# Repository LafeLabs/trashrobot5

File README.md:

## [link up a level../](../)

# Trash robot

## UNO Shield

[link to page on pcbway to buy board](https://www.pcbway.com/project/shareproject/Generic_Trash_Robot_UNO_Shield__V5.html)

## UNO Shield BOM

| REFDES|value| source/part#| 
|-------|-----|-------------|
|   R1  | 10k | [digikey RNCP0603FTD10K0CT-ND](https://www.digikey.com/product-detail/en/panasonic-electronic-components/ERJ-3EKF3301V/P3.30KHCT-ND/1746762)  | 
|   R2  | 10k | [digikey RNCP0603FTD10K0CT-ND](https://www.digikey.com/product-detail/en/panasonic-electronic-components/ERJ-3EKF3301V/P3.30KHCT-ND/1746762)  | 
|   R3  | 10k | [digikey RNCP0603FTD10K0CT-ND](https://www.digikey.com/product-detail/en/panasonic-electronic-components/ERJ-3EKF3301V/P3.30KHCT-ND/1746762)  | 
|   R4  | 300 | [digikey RR08P300DCT-ND](https://www.digikey.com/product-detail/en/susumu/RR0816P-301-D/RR08P300DCT-ND/432711)  | 
|   R5  |10k pot| [digikey PTV09A-4225F-B103-ND](https://www.digikey.com/product-detail/en/bourns-inc/PTV09A-4225F-B103/PTV09A-4225F-B103-ND/3781155)  | 
|   Q1  |MOSFET| [digikey IRLML0060TRPBFCT-ND](https://www.digikey.com/product-detail/en/infineon-technologies/IRLML0060TRPBF/IRLML0060TRPBFCT-ND/2202229)  | 
|   D1  |DIODE| [digikey S1BFSCT-ND](https://www.digikey.com/product-detail/en/on-semiconductor/S1B/S1BFSCT-ND/965719)  | 
|   C1  |1000uF| [digikey 1189-1745-ND](https://www.digikey.com/product-detail/en/rubycon/35PX1000MEFC10X20/1189-1745-ND/3563769)  | 
|   X1  |CONTACT| [digikey 277-6354-ND](https://www.digikey.com/product-detail/en/phoenix-contact/1984963/277-6354-ND/2513976)  | 
|   X2  |CONTACT| [digikey 277-6354-ND](https://www.digikey.com/product-detail/en/phoenix-contact/1984963/277-6354-ND/2513976)  | 
|   X3  |CONTACT| [digikey 277-6354-ND](https://www.digikey.com/product-detail/en/phoenix-contact/1984963/277-6354-ND/2513976)  | 
|   SW1  |BUTTON| [digikey P15931SCT-ND](https://www.digikey.com/product-detail/en/panasonic-electronic-components/EVQ-11D05B/P15931SCT-ND/3873336)  | 
|   SW2  |BUTTON| [digikey P15931SCT-ND](https://www.digikey.com/product-detail/en/panasonic-electronic-components/EVQ-11D05B/P15931SCT-ND/3873336)  | 
|   SW3  |SPDT| [digikey 360-1013-ND](https://www.digikey.com/product-detail/en/nkk-switches/B13AP/360-1013-ND/379100)  | 
|   J1  |3x HEADERS| [digikey SAM1029-03-ND](https://www.digikey.com/product-detail/en/samtec-inc/TSW-103-07-G-S/SAM1029-03-ND/1101324)| 
|   J2  |4x HEADERS| [digikey SAM1029-04-ND](https://www.digikey.com/product-detail/en/samtec-inc/TSW-104-07-G-S/SAM1029-04-ND/1101323)| 
|   J3  |5x HEADERS| [digikey SAM1029-05-ND](https://www.digikey.com/product-detail/en/samtec-inc/TSW-105-07-G-S/SAM1029-05-ND/1101322)| 
|   J4  |ARDUINO HEADERS| [digikey 1528-1074-ND](https://www.digikey.com/product-detail/en/adafruit-industries-llc/85/1528-1074-ND/5154649)|
|   JS1  |3X SOCKET| [digikey SAM1206-03-ND](https://www.digikey.com/product-detail/en/samtec-inc/SSQ-103-03-T-S/SAM1206-03-ND/1111955)|
|   JS2  |4X SOCKET| [digikey SAM1206-04-ND](https://www.digikey.com/product-detail/en/samtec-inc/SSQ-104-03-T-S/SAM1206-04-ND/1111954)|
|   JS3  |5X SOCKET| [digikey SAM1206-05-ND](https://www.digikey.com/product-detail/en/samtec-inc/SSQ-105-03-T-S/SAM1206-05-ND/1111953)|

## Dual H Bridge

[link to buy on PCBway](https://www.pcbway.com/project/shareproject/Dual_H_Bridge__V_5.html)

## Dual H Bridge BOM

| REFDES|value| source/part#| 
|-------|-----|-------------|
|   R1  | 10k | [digikey RNCP0603FTD10K0CT-ND](https://www.digikey.com/product-detail/en/panasonic-electronic-components/ERJ-3EKF3301V/P3.30KHCT-ND/1746762)  | 
|   R2  | 10k | [digikey RNCP0603FTD10K0CT-ND](https://www.digikey.com/product-detail/en/panasonic-electronic-components/ERJ-3EKF3301V/P3.30KHCT-ND/1746762)  | 
|   R3  | 10k | [digikey RNCP0603FTD10K0CT-ND](https://www.digikey.com/product-detail/en/panasonic-electronic-components/ERJ-3EKF3301V/P3.30KHCT-ND/1746762)  | 
|   R4  | 10k | [digikey RNCP0603FTD10K0CT-ND](https://www.digikey.com/product-detail/en/panasonic-electronic-components/ERJ-3EKF3301V/P3.30KHCT-ND/1746762)  | 
|   Q1  |MOSFET| [digikey IRLML0060TRPBFCT-ND](https://www.digikey.com/product-detail/en/infineon-technologies/IRLML0060TRPBF/IRLML0060TRPBFCT-ND/2202229)  | 
|   Q2  |MOSFET| [digikey IRLML0060TRPBFCT-ND](https://www.digikey.com/product-detail/en/infineon-technologies/IRLML0060TRPBF/IRLML0060TRPBFCT-ND/2202229)  | 
|   Q3  |MOSFET| [digikey IRLML0060TRPBFCT-ND](https://www.digikey.com/product-detail/en/infineon-technologies/IRLML0060TRPBF/IRLML0060TRPBFCT-ND/2202229)  | 
|   Q4  |MOSFET| [digikey IRLML0060TRPBFCT-ND](https://www.digikey.com/product-detail/en/infineon-technologies/IRLML0060TRPBF/IRLML0060TRPBFCT-ND/2202229)  | 
|   Q5  |MOSFET| [digikey IRLML0060TRPBFCT-ND](https://www.digikey.com/product-detail/en/infineon-technologies/IRLML0060TRPBF/IRLML0060TRPBFCT-ND/2202229)  | 
|   Q6  |MOSFET| [digikey IRLML0060TRPBFCT-ND](https://www.digikey.com/product-detail/en/infineon-technologies/IRLML0060TRPBF/IRLML0060TRPBFCT-ND/2202229)  | 
|   Q7  |MOSFET| [digikey IRLML0060TRPBFCT-ND](https://www.digikey.com/product-detail/en/infineon-technologies/IRLML0060TRPBF/IRLML0060TRPBFCT-ND/2202229)  | 
|   Q8  |MOSFET| [digikey IRLML0060TRPBFCT-ND](https://www.digikey.com/product-detail/en/infineon-technologies/IRLML0060TRPBF/IRLML0060TRPBFCT-ND/2202229)  | 
|   X1  |CONTACT| [digikey 277-6354-ND](https://www.digikey.com/product-detail/en/phoenix-contact/1984963/277-6354-ND/2513976)  | 
|   X2  |CONTACT| [digikey 277-6354-ND](https://www.digikey.com/product-detail/en/phoenix-contact/1984963/277-6354-ND/2513976)  | 
|   X3  |CONTACT| [digikey 277-6354-ND](https://www.digikey.com/product-detail/en/phoenix-contact/1984963/277-6354-ND/2513976)  | 
|   J1  |4x RA HEADERS| [digikey TSW-104-25-G-S-RA-ND](https://www.digikey.com/product-detail/en/samtec-inc/TSW-104-25-G-S-RA/TSW-104-25-G-S-RA-ND/7864906)| 
|   J2  |5x RA HEADERS| [digikey TSW-105-25-G-S-RA-ND](https://www.digikey.com/product-detail/en/samtec-inc/TSW-105-25-G-S-RA/TSW-105-25-G-S-RA-ND/2685928)| 
|   JS1  |4X SOCKET| [digikey SAM1206-04-ND](https://www.digikey.com/product-detail/en/samtec-inc/SSQ-104-03-T-S/SAM1206-04-ND/1111954)|
|   JS2  |5X SOCKET| [digikey SAM1206-05-ND](https://www.digikey.com/product-detail/en/samtec-inc/SSQ-105-03-T-S/SAM1206-05-ND/1111953)|

## Kit BOM

|Description|Link|
|-----------|----|
|Jumper Wires|[Digikey 1528-1160-ND](https://www.digikey.com/product-detail/en/adafruit-industries-llc/824/1528-1160-ND/5353620)|
|Solder Paste|[Digikey SMDLTLFP-ND](https://www.digikey.com/product-detail/en/chip-quik-inc/SMDLTLFP/SMDLTLFP-ND/2682721)|
|2.1X5 MM Barrel Breakout|[Digikey 839-1518-ND](https://www.digikey.com/product-detail/en/tensility-international-corp/10-02931/839-1518-ND/9686414)|
|2.1X5 MM Barrel patch cable|[Amazon $6.99](https://www.amazon.com/Valley-Enterprises%C2%AE-2-1mm-5-5mm-Adapter/dp/B00DX72UXW/)|
| 12V 12Ah LiPo|[Amazon $33.99](https://www.amazon.com/gp/product/B00ME3ZH7C/)|
| 12V 3Ah LiPo |[Amazon $24.19](https://www.amazon.com/TalentCell-Rechargeable-3000mAh-Lithium-External/dp/B01M7Z9Z1N/) |
|30 AWG Magnet wire|[Amazon $17.45](https://www.amazon.com/dp/B07SG4CPSF/) |
| Arduino Uno | [Amazon $8.49](https://www.amazon.com/HiLetgo-ATmega328P-Development-Compatible-Microcontroller/dp/B01AR7YJ3O/) |
| Hookup Wire Kit | [Adafruit $19.95](https://www.adafruit.com/product/3111) |
| 3 axis Accelerometer | [Adafruit $7.95](https://www.adafruit.com/product/2019) |
| I2C Pressure Sensor| [Adafruit $9.95](https://www.adafruit.com/product/2651) |
|ultrasonic range finder|[Sparkfun $3.95](https://www.sparkfun.com/products/15569)|
| Neopixel 8x array| [Adafruit $5.95](https://www.adafruit.com/product/1426) |
| Hot Air Rework Tool| [Sparkfun $129.95](https://www.sparkfun.com/products/14557) |
| Soldering Iron| [Sparkfun $129.00](https://www.sparkfun.com/products/14734) |
| Lead Free Solder| [Sparkfun $7.95](https://www.sparkfun.com/products/9325) |

- [boards/unoshield-v5.brd](boards/unoshield-v5.brd)
- [boards/unoshield-v5.sch](boards/unoshield-v5.sch)
- [boards/unoshield-v5-bom.xlsx](boards/unoshield-v5-bom.xlsx)
- [boards/dualHbridge-v5.brd](boards/dualHbridge-v5.brd)
- [boards/dualHbridge-v5.sch](boards/dualHbridge-v5.sch)
- [boards/dualHbridge-v5bom.xlsx](boards/dualHbridge-v5bom.xlsx)

### Cables:

- 4 conductor, 8 inches long, header to stripped and tinned ends with 1/4 inch stripping: [IDSS-04-S-08.00-ST4](https://www.samtec.com/products/idss-04-s-08.00-st4)
- 3 conductor, 8 inches long, header to stripped and tinned ends, with 1/4 inch stripping: [https://www.samtec.com/products/idss-03-s-08.00-st4](https://www.samtec.com/products/idss-03-s-08.00-st4)

# 90 degree terminal strips for dual h bridge:

5 pin:
TSW-105-25-G-S-RA	

4 pin:

TSW-104-25-G-S-RA

## 5 wire cable from shield to dual h bridge:

idss-05-d-06.00

## 4 wire cable to solder stripped ends for stepper motor and also I2C sensors(need as many of these as stepper motors plus I2 C sensors.):

IDSS-04-S-08.00-T	(8 inches)

## 3 wire cable with solder tinned ends for neopixels, 8 inch:

IDSS-03-S-08.00-T

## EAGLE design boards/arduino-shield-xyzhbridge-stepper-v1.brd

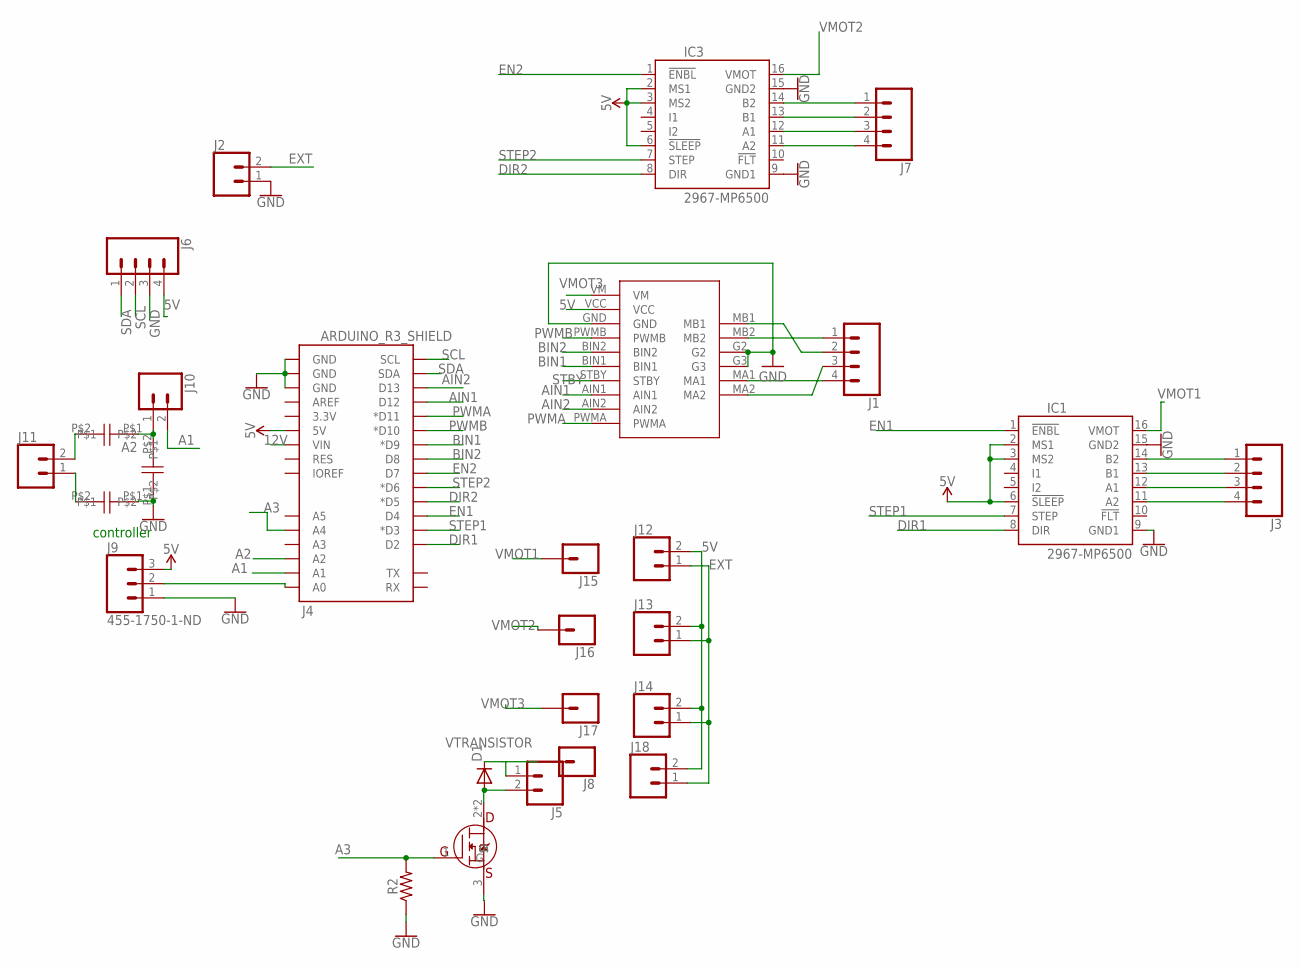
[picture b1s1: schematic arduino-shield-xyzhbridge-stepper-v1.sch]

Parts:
D1: DIODE-DO-214AC; DO-214AC
IC1, IC3: 2967-MP6500; MP6500
J1, J3, J6, J7: CONN_04; 1X04
J2, J5, J10, J11, J12, J13, J14, J18: CONN_02; 1X02
J4: ARDUINO_R3_SHIELD; UNO_R3_SHIELD
J8, J15, J16, J17: CONN_01; 1X01
J9: 455-1750-1-ND; 1X03
R2: AXIAL-0.3
U$1: ADAFRUIT-TB6612
U$2, U$3, U$4: AXIALCAP
U$5: IRFL024NPBF; SOT223

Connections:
5V: IC1.2 (MS1), IC1.3 (MS2), IC1.6 (!SLEEP), IC3.2 (MS1), IC3.3 (MS2), IC3.6 (!SLEEP), J4.5V, J6.4, J9.3, J12.2, J13.2, J14.2, J18.2, U$1.VCC
12V: J4.VIN
A1: J4.A1, J10.2
A2: J4.A2, J10.1, U$3.P$2, U$4.P$1
A3: J4.A4, R2.P$2 (2), U$5.1 (G)
AIN1: J4.D12, U$1.AIN1
AIN2: J4.D13, U$1.AIN2
BIN1: J4.D9 (*D9), U$1.BIN1
BIN2: J4.D8, U$1.BIN2
DIR1: IC1.8 (DIR), J4.D2
DIR2: IC3.8 (DIR), J4.D5 (*D5)
EN1: IC1.1 (!ENBL), J4.D4
EN2: IC3.1 (!ENBL), J4.D7
EXT: J2.2, J12.1, J13.1, J14.1, J18.1
GND: IC1.9 (GND1), IC1.15 (GND2), IC3.9 (GND1), IC3.15 (GND2), J2.1, J4.GND@0 (GND), J4.GND@1 (GND), J4.GND@2 (GND), J6.3, J9.1, R2.P$1 (1), U$1.G2, U$1.G3, U$1.GND, U$2.P$1, U$3.P$1, U$5.3 (S)
unnamed: IC3.14 (B2), J7.1
unnamed: IC3.13 (B1), J7.2
unnamed: IC1.14 (B2), J3.1
unnamed: IC1.13 (B1), J3.2
unnamed: IC1.12 (A1), J3.3
unnamed: IC1.11 (A2), J3.4
unnamed: J1.2, U$1.MB1
unnamed: J1.1, U$1.MB2
unnamed: IC3.12 (A1), J7.3
unnamed: IC3.11 (A2), J7.4
unnamed: J4.A0, J9.2
unnamed: J1.4, U$1.MA1
unnamed: J1.3, U$1.MA2
unnamed: D1.A, J5.2, U$5.2 (D), U$5.4 (D)
unnamed: J11.2, U$4.P$2
unnamed: J11.1, U$2.P$2
PWMA: J4.D11 (*D11), U$1.PWMA
PWMB: J4.D10 (*D10), U$1.PWMB
SCL: J4.SCL, J6.2
SDA: J4.SDA, J6.1
STBY: U$1.STBY
STEP1: IC1.7 (STEP), J4.D3 (*D3)
STEP2: IC3.7 (STEP), J4.D6 (*D6)
VMOT1: IC1.16 (VMOT), J15.1
VMOT2: IC3.16 (VMOT), J16.1
VMOT3: J17.1, U$1.VM
VTRANSISTOR: D1.C, J5.1, J8.1

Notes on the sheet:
controller

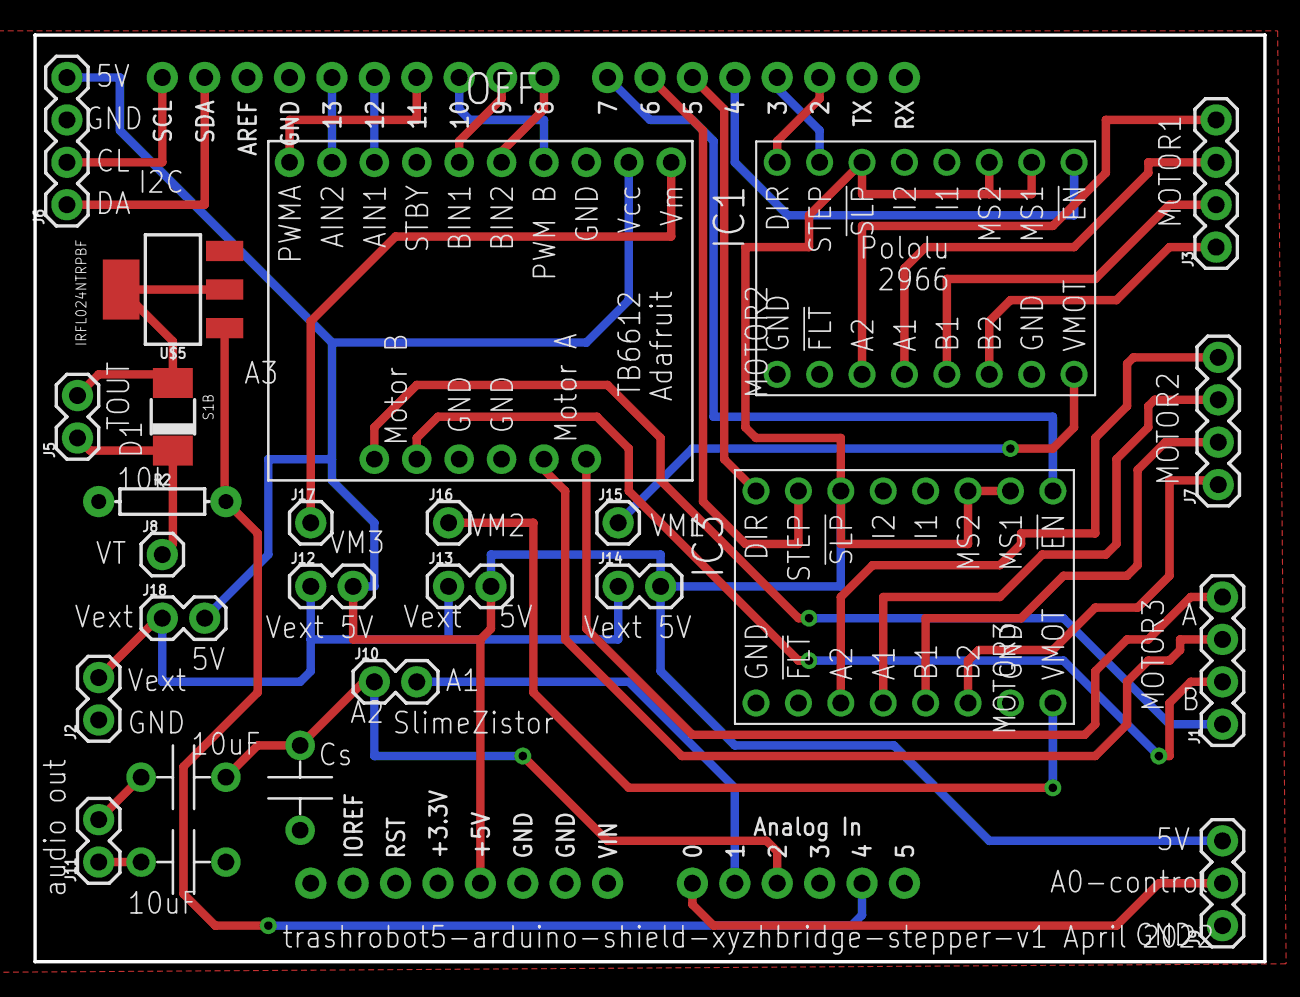
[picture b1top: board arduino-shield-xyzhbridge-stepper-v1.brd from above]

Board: 2 copper layers, 73.7 x 55.5 mm, 27 parts (0 on the bottom side), 40 nets.

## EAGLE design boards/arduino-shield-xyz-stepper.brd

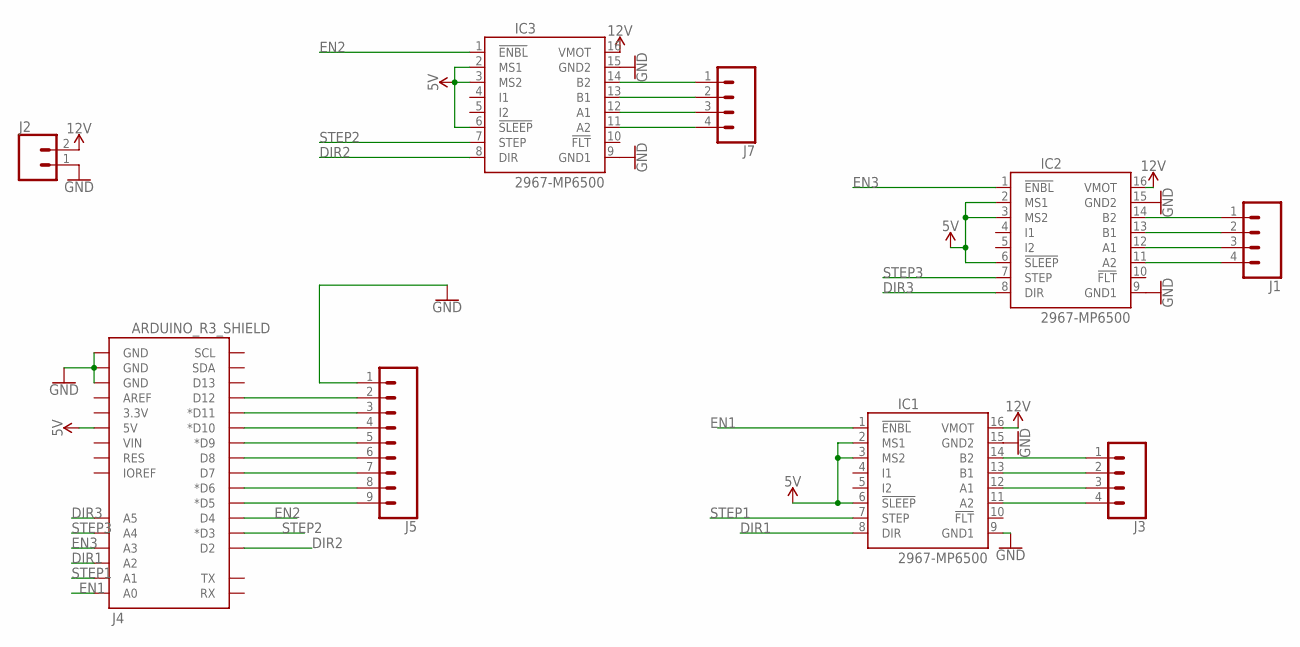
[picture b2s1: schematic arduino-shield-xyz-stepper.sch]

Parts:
IC1, IC2, IC3: 2967-MP6500; MP6500
J1, J3, J7: CONN_04; 1X04
J2: CONN_02; 1X02
J4: ARDUINO_R3_SHIELD; UNO_R3_SHIELD
J5: CONN_09; 1X09

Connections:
5V: IC1.2 (MS1), IC1.3 (MS2), IC1.6 (!SLEEP), IC2.2 (MS1), IC2.3 (MS2), IC2.6 (!SLEEP), IC3.2 (MS1), IC3.3 (MS2), IC3.6 (!SLEEP), J4.5V
12V: IC1.16 (VMOT), IC2.16 (VMOT), IC3.16 (VMOT), J2.2
DIR1: IC1.8 (DIR), J4.A2
DIR2: IC3.8 (DIR), J4.D2
DIR3: IC2.8 (DIR), J4.A5
EN1: IC1.1 (!ENBL), J4.A0
EN2: IC3.1 (!ENBL), J4.D4
EN3: IC2.1 (!ENBL), J4.A3
GND: IC1.9 (GND1), IC1.15 (GND2), IC2.9 (GND1), IC2.15 (GND2), IC3.9 (GND1), IC3.15 (GND2), J2.1, J4.GND@0 (GND), J4.GND@1 (GND), J4.GND@2 (GND), J5.1
unnamed: IC3.14 (B2), J7.1
unnamed: IC3.13 (B1), J7.2
unnamed: IC1.14 (B2), J3.1
unnamed: IC1.13 (B1), J3.2
unnamed: IC1.12 (A1), J3.3
unnamed: IC1.11 (A2), J3.4
unnamed: IC2.14 (B2), J1.1
unnamed: IC2.13 (B1), J1.2
unnamed: IC2.12 (A1), J1.3
unnamed: IC2.11 (A2), J1.4
unnamed: IC3.12 (A1), J7.3
unnamed: IC3.11 (A2), J7.4
unnamed: J4.D12, J5.2
unnamed: J4.D11 (*D11), J5.3
unnamed: J4.D10 (*D10), J5.4
unnamed: J4.D9 (*D9), J5.5
unnamed: J4.D8, J5.6
unnamed: J4.D7, J5.7
unnamed: J4.D6 (*D6), J5.8
unnamed: J4.D5 (*D5), J5.9
STEP1: IC1.7 (STEP), J4.A1
STEP2: IC3.7 (STEP), J4.D3 (*D3)
STEP3: IC2.7 (STEP), J4.A4

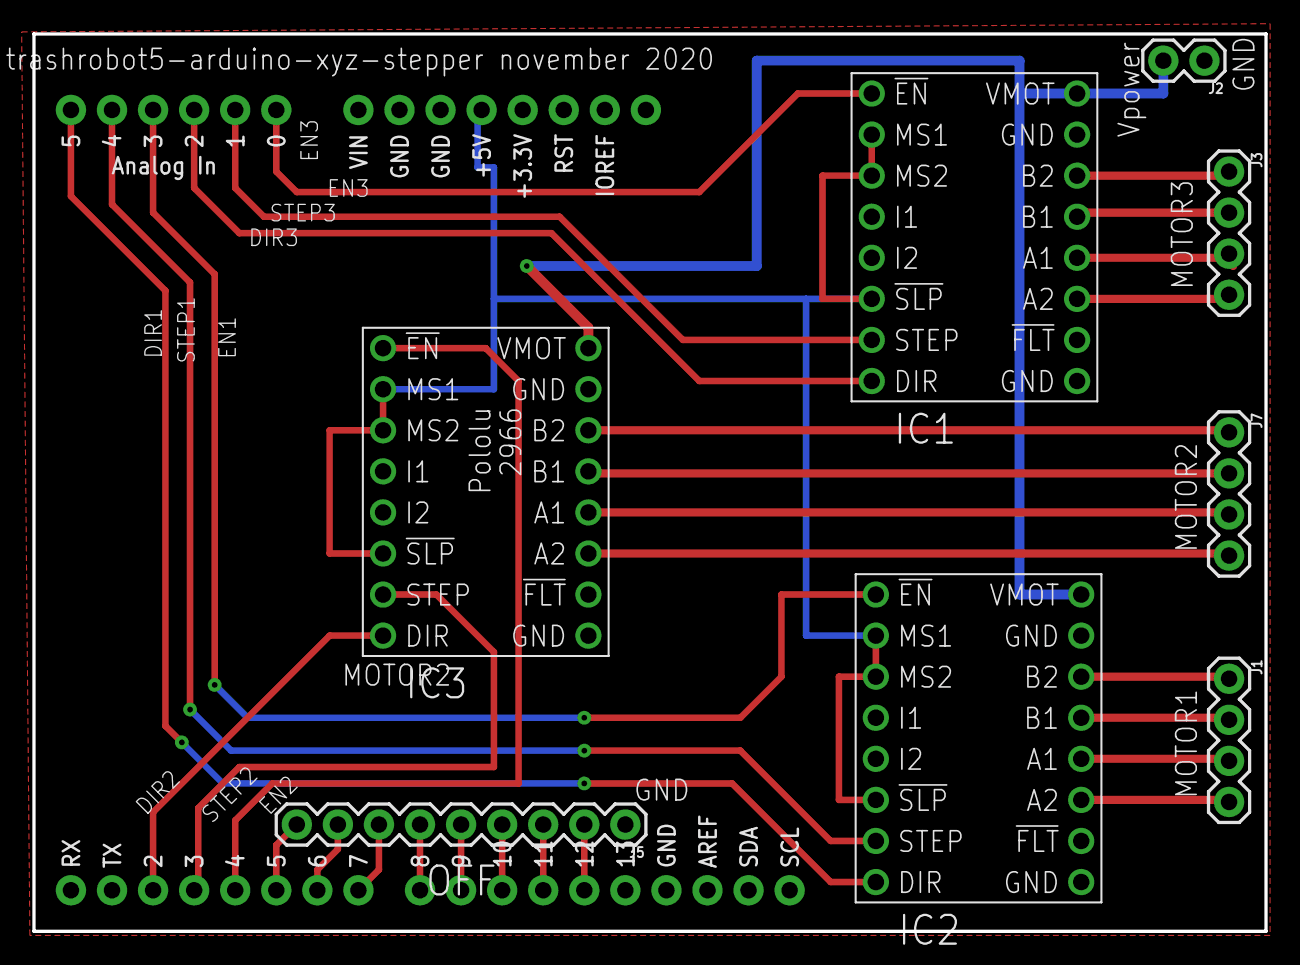
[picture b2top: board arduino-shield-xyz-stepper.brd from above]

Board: 2 copper layers, 76.2 x 55.5 mm, 9 parts (0 on the bottom side), 32 nets.

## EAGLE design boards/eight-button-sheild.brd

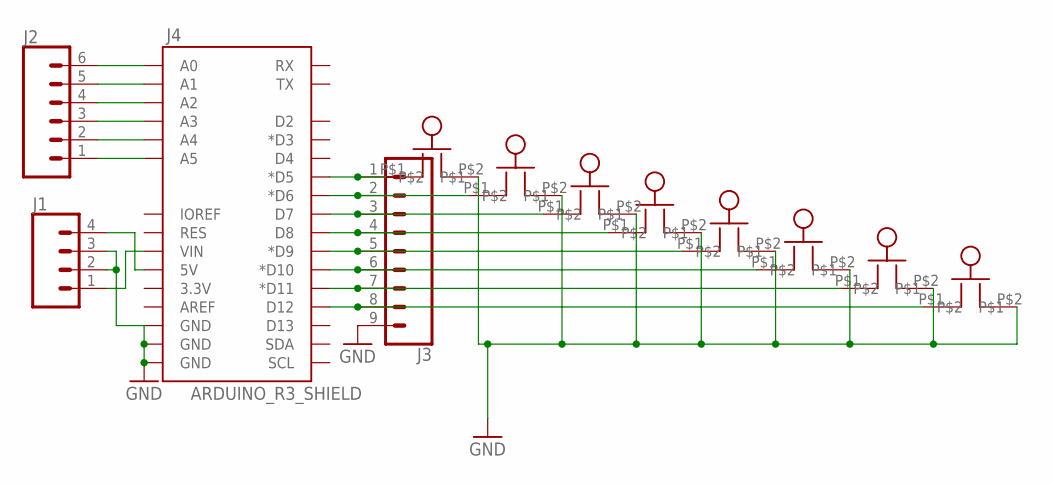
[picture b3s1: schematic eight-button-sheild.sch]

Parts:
J1: CONN_04; 1X04
J2: CONN_06SILK_FEMALE_PTH; 1X06
J3: CONN_09; 1X09
J4: ARDUINO_R3_SHIELD; UNO_R3_SHIELD
SW1, SW2, SW3, SW4, SW5, SW6, SW7, SW8: BUTTON

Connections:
GND: J1.2, J1.3, J3.9, J4.GND@0 (GND), J4.GND@1 (GND), J4.GND@2 (GND), SW1.P$2, SW2.P$2, SW3.P$2, SW4.P$2, SW5.P$2, SW6.P$2, SW7.P$2, SW8.P$2
unnamed: J3.1, J4.D5 (*D5), SW1.P$1
unnamed: J3.2, J4.D6 (*D6), SW2.P$1
unnamed: J3.3, J4.D7, SW3.P$1
unnamed: J3.4, J4.D8, SW4.P$1
unnamed: J3.5, J4.D9 (*D9), SW5.P$1
unnamed: J3.6, J4.D10 (*D10), SW6.P$1
unnamed: J2.1, J4.A5
unnamed: J3.7, J4.D11 (*D11), SW7.P$1
unnamed: J3.8, J4.D12, SW8.P$1
unnamed: J2.2, J4.A4
unnamed: J2.3, J4.A3
unnamed: J2.4, J4.A2
unnamed: J2.5, J4.A1
unnamed: J2.6, J4.A0
unnamed: J1.1, J4.VIN
unnamed: J1.4, J4.5V

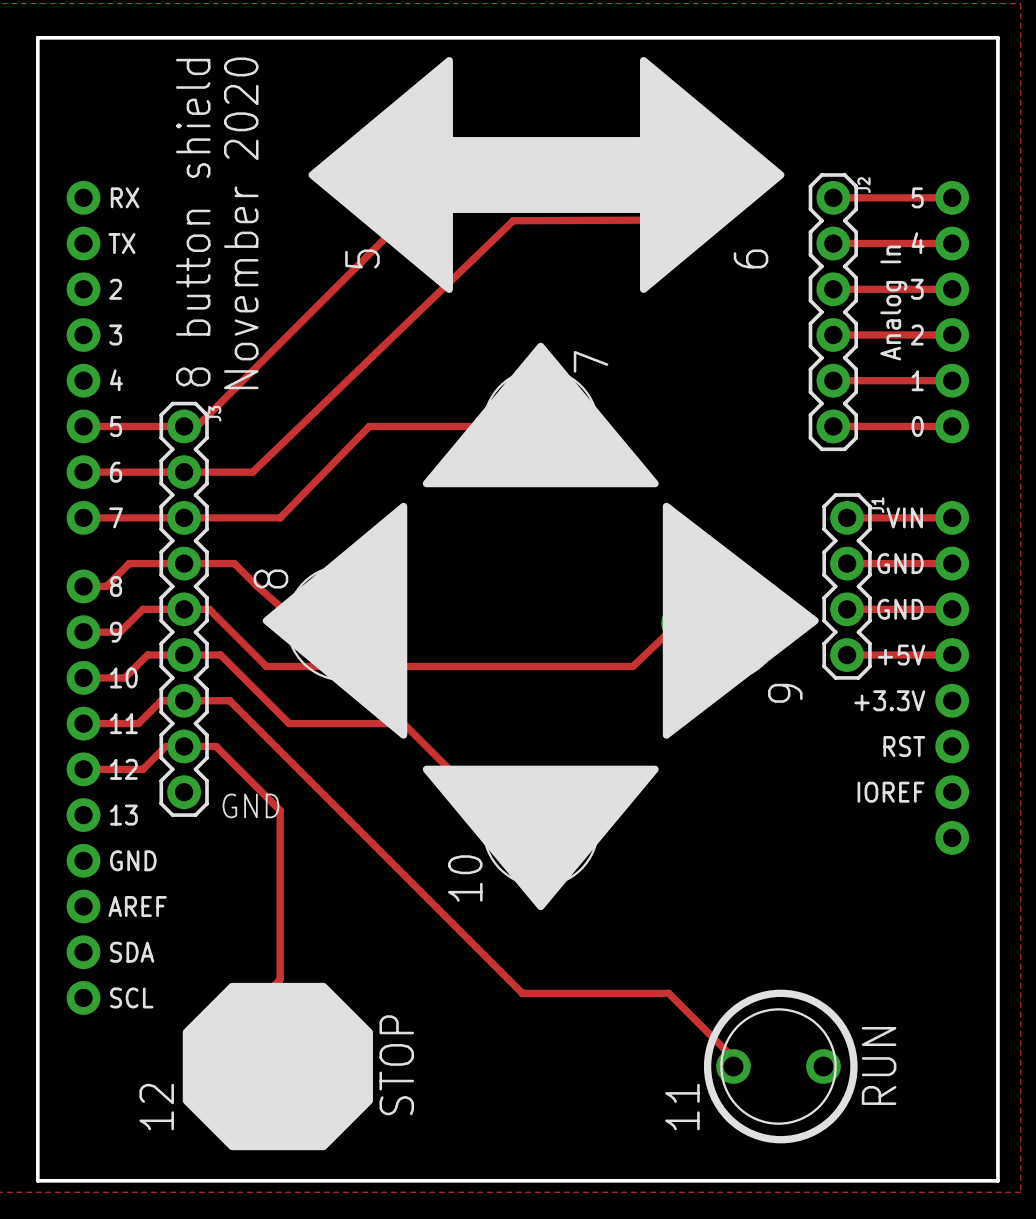
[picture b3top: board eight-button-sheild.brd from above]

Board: 2 copper layers, 53.3 x 63.5 mm, 12 parts (0 on the bottom side), 17 nets.

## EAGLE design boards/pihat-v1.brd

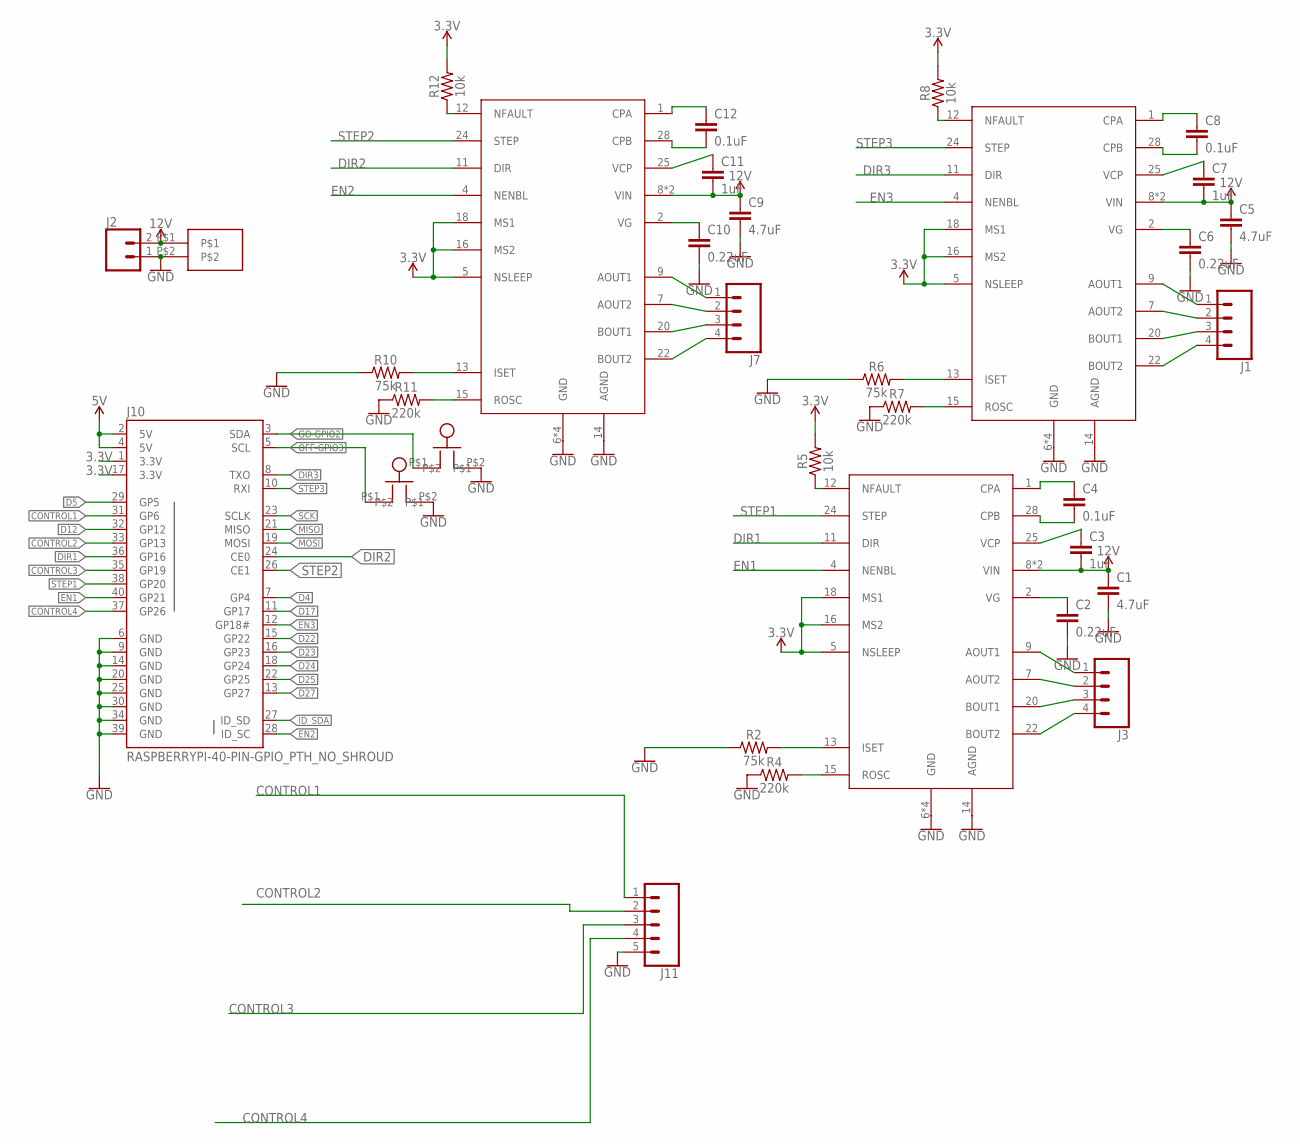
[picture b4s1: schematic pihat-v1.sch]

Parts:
C1, C5, C9: 4.7uF; 0603
C2, C6, C10: 0.22uF; 0603
C3, C7, C11: 1uF; 0603
C4, C8, C12: 0.1uF; 0603
J1, J3, J7: CONN_04; 1X04
J2: CONN_02; 1X02
J10: RASPBERRYPI-40-PIN-GPIO_PTH_NO_SHROUD; 2X20
J11: CONN_05; 1X05
R2, R6, R10: 75k; 0603
R4, R7, R11: 220k; 0603
R5, R8, R12: 10k; 0603
U$1, U$2, U$3: MP6500MP6500; TSSOP28
U$4, U$5: BUTTON
U$6: SPRING-TERMINAL

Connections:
3.3V: J10.1 (3.3V), J10.17 (3.3V), R5.2, R8.2, R12.2, U$1.5 (NSLEEP), U$1.16 (MS2), U$1.18 (MS1), U$2.5 (NSLEEP), U$2.16 (MS2), U$2.18 (MS1), U$3.5 (NSLEEP), U$3.16 (MS2), U$3.18 (MS1)
5V: J10.2 (5V), J10.4 (5V)
12V: C1.1, C3.2, C5.1, C7.2, C9.1, C11.2, J2.2, U$1.8 (VIN), U$1.21 (VIN), U$2.8 (VIN), U$2.21 (VIN), U$3.8 (VIN), U$3.21 (VIN), U$6.P$1
CONTROL1: J10.31 (GP6), J11.1
CONTROL2: J10.33 (GP13), J11.2
CONTROL3: J10.35 (GP19), J11.3
CONTROL4: J10.37 (GP26), J11.4
D4: J10.7 (GP4)
D5: J10.29 (GP5)
D12: J10.32 (GP12)
D17: J10.11 (GP17)
D22: J10.15 (GP22)
D23: J10.16 (GP23)
D24: J10.18 (GP24)
D25: J10.22 (GP25)
D27: J10.13 (GP27)
DIR1: J10.36 (GP16), U$3.11 (DIR)
DIR2: J10.24 (CE0), U$2.11 (DIR)
DIR3: J10.8 (TXO), U$1.11 (DIR)
EN1: J10.40 (GP21), U$3.4 (NENBL)
EN2: J10.28 (ID_SC), U$2.4 (NENBL)
EN3: J10.12 (GP18#), U$1.4 (NENBL)
GND: C1.2, C2.2, C5.2, C6.2, C9.2, C10.2, J2.1, J10.6 (GND), J10.9 (GND), J10.14 (GND), J10.20 (GND), J10.25 (GND), J10.30 (GND), J10.34 (GND), J10.39 (GND), J11.5, R2.1, R4.1, R6.1, R7.1, R10.1, R11.1, U$1.6 (GND), U$1.10 (GND), U$1.14 (AGND), U$1.19 (GND), U$1.23 (GND), U$2.6 (GND), U$2.10 (GND), U$2.14 (AGND), U$2.19 (GND), U$2.23 (GND), U$3.6 (GND), U$3.10 (GND), U$3.14 (AGND), U$3.19 (GND), U$3.23 (GND), U$4.P$2, U$5.P$2, U$6.P$2
GO-GPIO2: J10.3 (SDA), U$4.P$1
ID_SDA: J10.27 (ID_SD)
MISO: J10.21 (MISO)
MOSI: J10.19 (MOSI)
unnamed: J3.1, U$3.9 (AOUT1)
unnamed: J3.2, U$3.7 (AOUT2)
unnamed: J3.3, U$3.20 (BOUT1)
unnamed: J3.4, U$3.22 (BOUT2)
unnamed: J1.1, U$1.9 (AOUT1)
unnamed: J1.2, U$1.7 (AOUT2)
unnamed: J1.3, U$1.20 (BOUT1)
unnamed: J1.4, U$1.22 (BOUT2)
unnamed: C7.1, U$1.25 (VCP)
unnamed: C6.1, U$1.2 (VG)
unnamed: C8.1, U$1.1 (CPA)
unnamed: C8.2, U$1.28 (CPB)
unnamed: R5.1, U$3.12 (NFAULT)
unnamed: C3.1, U$3.25 (VCP)
unnamed: C2.1, U$3.2 (VG)
unnamed: C4.1, U$3.1 (CPA)
unnamed: C4.2, U$3.28 (CPB)
unnamed: R2.2, U$3.13 (ISET)
unnamed: R4.2, U$3.15 (ROSC)
unnamed: R7.2, U$1.15 (ROSC)
unnamed: R8.1, U$1.12 (NFAULT)
unnamed: R6.2, U$1.13 (ISET)
unnamed: J7.1, U$2.9 (AOUT1)
unnamed: J7.2, U$2.7 (AOUT2)
unnamed: J7.3, U$2.20 (BOUT1)
unnamed: J7.4, U$2.22 (BOUT2)
unnamed: C11.1, U$2.25 (VCP)
unnamed: C10.1, U$2.2 (VG)
unnamed: C12.1, U$2.1 (CPA)
unnamed: C12.2, U$2.28 (CPB)
unnamed: R11.2, U$2.15 (ROSC)
unnamed: R12.1, U$2.12 (NFAULT)
unnamed: R10.2, U$2.13 (ISET)
OFF-GPIO3: J10.5 (SCL), U$5.P$1
SCK: J10.23 (SCLK)
STEP1: J10.38 (GP20), U$3.24 (STEP)
STEP2: J10.26 (CE1), U$2.24 (STEP)
STEP3: J10.10 (RXI), U$1.24 (STEP)

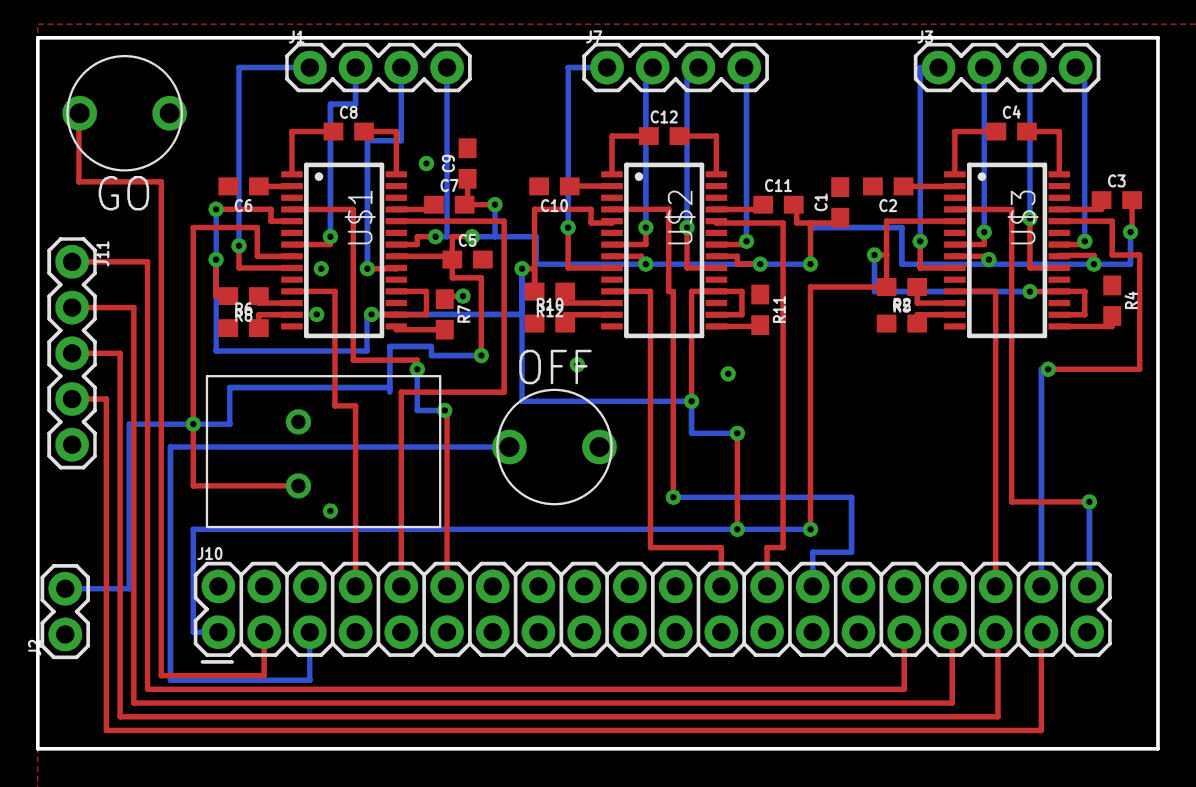
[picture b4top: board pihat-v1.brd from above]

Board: 2 copper layers, 62.2 x 39.5 mm, 33 parts (0 on the bottom side), 52 nets.

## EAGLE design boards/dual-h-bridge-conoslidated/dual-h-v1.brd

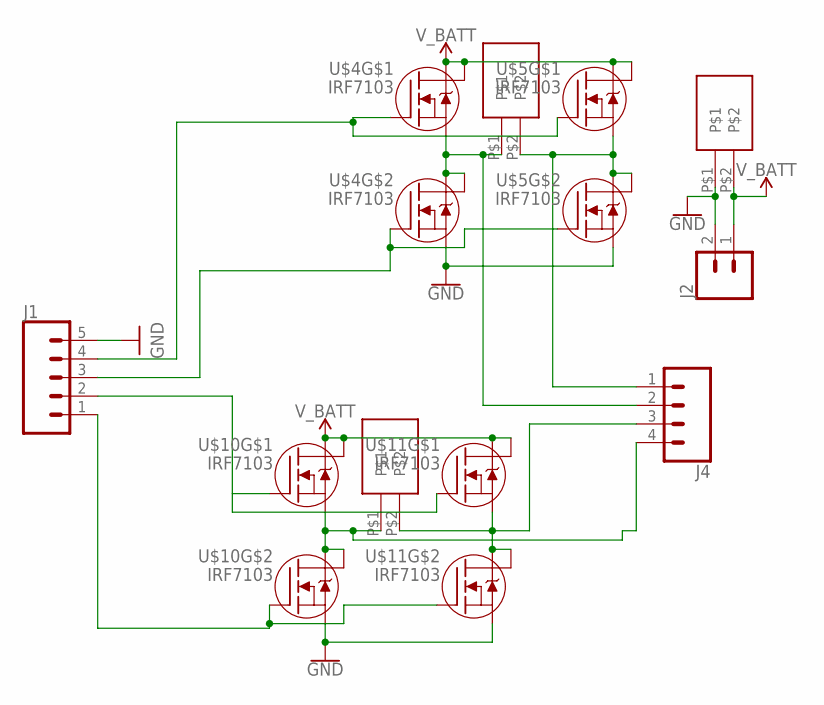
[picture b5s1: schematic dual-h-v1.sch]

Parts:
J1: CONN_05; 1X05
J2: CONN_02; 1X02
J4: CONN_04; 1X04
U$1, U$6, U$12: SPRING-TERMINAL
U$4, U$5, U$10, U$11: IRF7103; SO8-2

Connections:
GND: J1.5, J2.2, U$1.P$1, U$4.3 (S), U$5.3 (S), U$10.3 (S), U$11.3 (S)
unnamed: J4.4, U$10.1 (S), U$10.5 (D), U$10.6 (D), U$12.P$1
unnamed: J4.2, U$4.1 (S), U$4.5 (D), U$4.6 (D), U$6.P$1
unnamed: J4.1, U$5.1 (S), U$5.5 (D), U$5.6 (D), U$6.P$2
unnamed: J1.4, U$4.2 (G), U$5.2 (G)
unnamed: J1.1, U$10.4 (G), U$11.4 (G)
unnamed: J1.3, U$4.4 (G), U$5.4 (G)
unnamed: J4.3, U$11.1 (S), U$11.5 (D), U$11.6 (D), U$12.P$2
unnamed: J1.2, U$10.2 (G), U$11.2 (G)
V_BATT: J2.1, U$1.P$2, U$4.7 (D), U$4.8 (D), U$5.7 (D), U$5.8 (D), U$10.7 (D), U$10.8 (D), U$11.7 (D), U$11.8 (D)

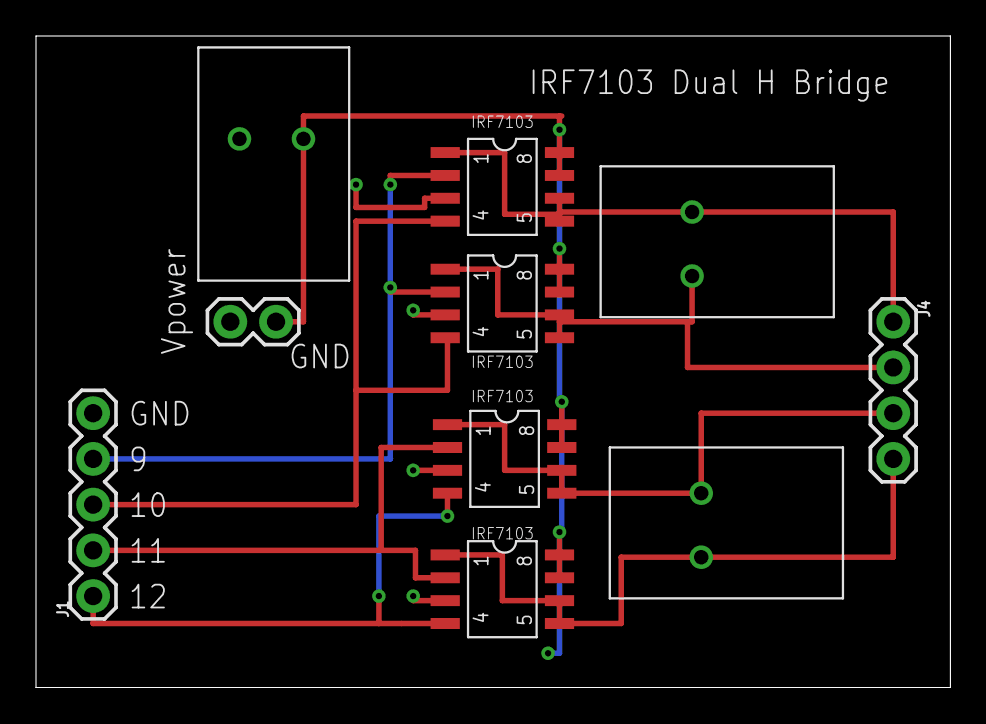
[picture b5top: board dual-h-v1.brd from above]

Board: 2 copper layers, 50.8 x 36.2 mm, 10 parts (0 on the bottom side), 10 nets.

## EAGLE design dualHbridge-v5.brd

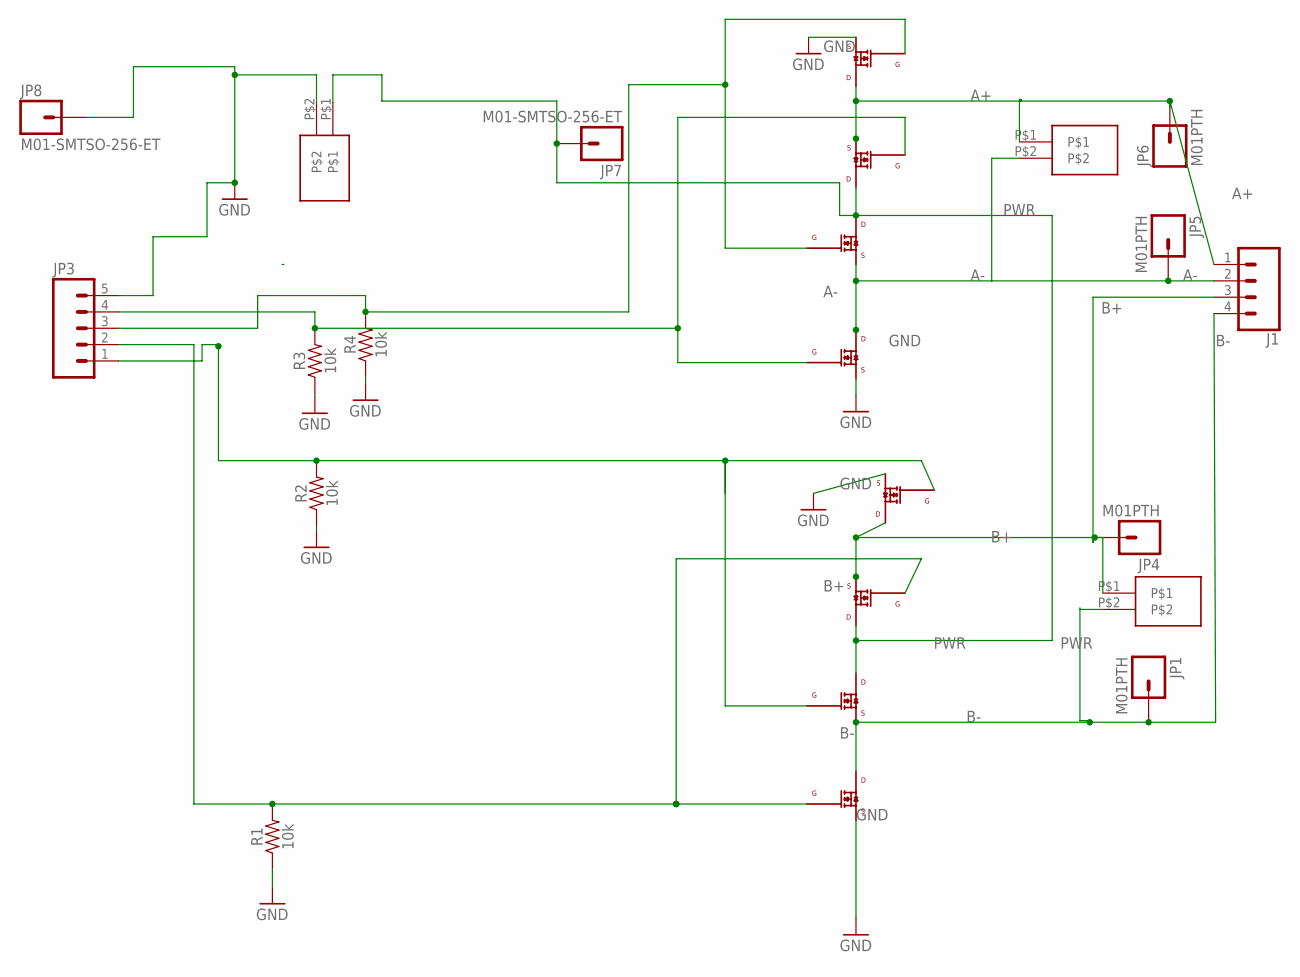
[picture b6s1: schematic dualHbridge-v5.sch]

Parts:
J1: CONN_04; 1X04
JP1, JP4, JP5, JP6: M01PTH; 1X01@1
JP3: M05PTH; 1X05
JP7, JP8: M01-SMTSO-256-ET; SMTSO-256-ET
Q1, Q2, Q3, Q4, Q5, Q6, Q7, Q8: IRLML0060; SOT-23
R1, R2, R3, R4: 10k; 0603
X1, X2, X3: SPRING-TERMINAL

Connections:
A+: J1.1, JP6.1, Q1.3 (DRAIN), Q2.2 (SOURCE), X1.P$1
A-: J1.2, JP5.1, Q3.2 (SOURCE), Q4.3 (DRAIN), X1.P$2
B+: J1.3, JP4.1, Q5.3 (DRAIN), Q6.2 (SOURCE), X2.P$1
B-: J1.4, JP1.1, Q7.2 (SOURCE), Q8.3 (DRAIN), X2.P$2
GND: JP3.5, JP8.P$1, Q1.2 (SOURCE), Q4.2 (SOURCE), Q5.2 (SOURCE), Q8.2 (SOURCE), R1.1, R2.1, R3.1, R4.1, X3.P$2
unnamed: JP3.4, Q2.1 (GATE), Q4.1 (GATE), R3.2
unnamed: JP3.3, Q1.1 (GATE), Q3.1 (GATE), R4.2
unnamed: JP3.1, Q5.1 (GATE), Q7.1 (GATE), R2.2
unnamed: JP3.2, Q6.1 (GATE), Q8.1 (GATE), R1.2
PWR: JP7.P$1, Q2.3 (DRAIN), Q3.3 (DRAIN), Q6.3 (DRAIN), Q7.3 (DRAIN), X3.P$1

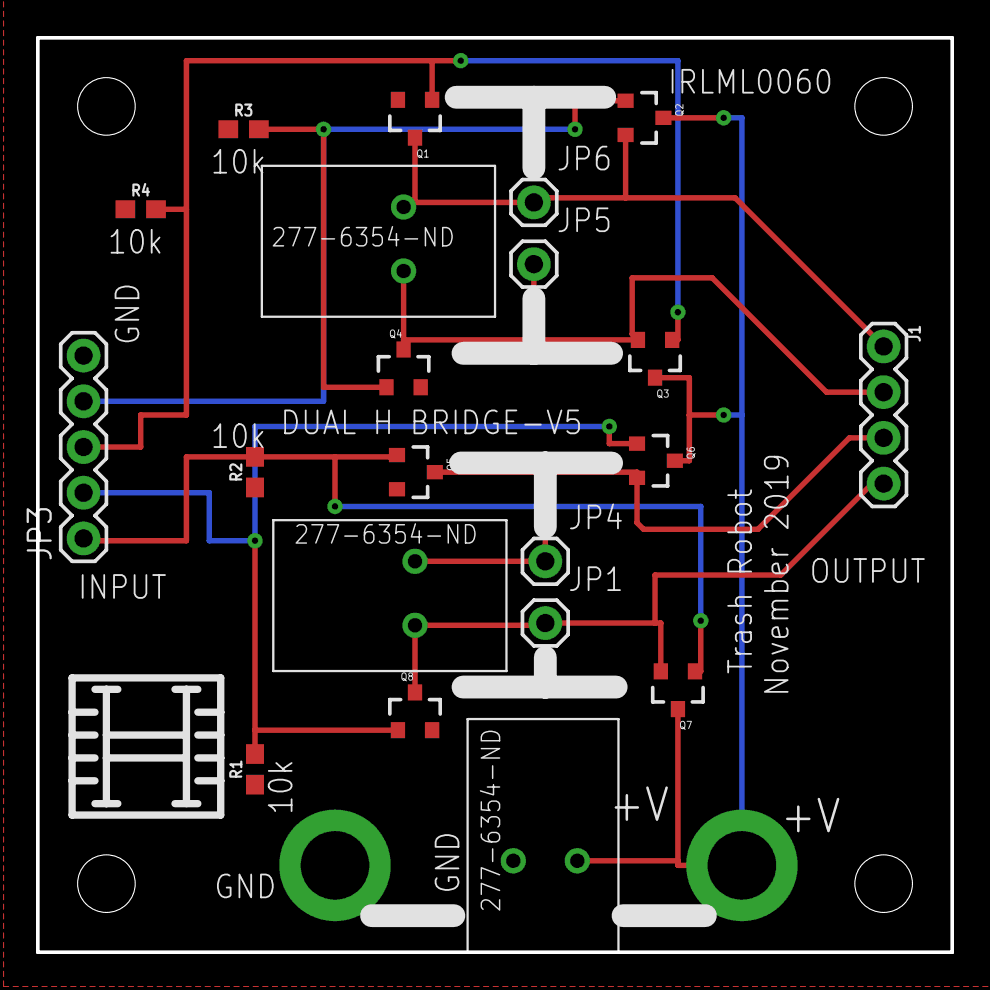
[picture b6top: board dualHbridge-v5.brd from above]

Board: 2 copper layers, 50.8 x 50.8 mm, 23 parts (0 on the bottom side), 10 nets.

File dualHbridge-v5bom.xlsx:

REFDES | Value | QTY | Manufacturer | Manufacturer Part Number | Digikey Part Number | package | Price
Q1 | IRLML0060 | 1 | Infineon | IRLML0060 | IRLML0060TRPBFCT-ND |  | 0.25
Q2 | IRLML0060 | 1 | Infineon | IRLML0060 | IRLML0060TRPBFCT-ND |  | 0.25
Q3 | IRLML0060 | 1 | Infineon | IRLML0060 | IRLML0060TRPBFCT-ND |  | 0.25
Q4 | IRLML0060 | 1 | Infineon | IRLML0060 | IRLML0060TRPBFCT-ND |  | 0.25
Q5 | IRLML0060 | 1 | Infineon | IRLML0060 | IRLML0060TRPBFCT-ND |  | 0.25
Q6 | IRLML0060 | 1 | Infineon | IRLML0060 | IRLML0060TRPBFCT-ND |  | 0.25
Q7 | IRLML0060 | 1 | Infineon | IRLML0060 | IRLML0060TRPBFCT-ND |  | 0.25
Q8 | IRLML0060 | 1 | Infineon | IRLML0060 | IRLML0060TRPBFCT-ND |  | 0.25
X1 | spring contact | 3 | Phoenix Contact | 1984963 | 277-6354-ND
X2 |  |  | Phoenix Contact | 1984963 | 277-6354-ND
X3 |  |  | Phoenix Contact | 1984963 | 277-6354-ND
R1 | 10k | 4 | stackpole electronics | ERJ-3EKF3301V | RNCP0603FTD10K0CT-ND | 0603 | 2.7E-2
R2 | 10k |  | stackpole electronics | ERJ-3EKF3301V | RNCP0603FTD10K0CT-ND | 0603 | 2.7E-2
R3 | 10k |  | stackpole electronics | ERJ-3EKF3301V | RNCP0603FTD10K0CT-ND | 0603 | 2.7E-2
R4 | 10k |  | stackpole electronics | ERJ-3EKF3301V | RNCP0603FTD10K0CT-ND | 0603 | 2.7E-2
J1 | 4 pin header | 1 | Samtec | TSW-104-25-G-S-RA |  |  | 0.25
J1 | 5 pin header | 1 | Samtec | TSW-105-25-G-S-RA |  |  | 0.25
total |  |  |  |  |  |  | 2

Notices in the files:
parts and their libraries:
SparkFun-Connectors: Licensing: Creative Commons ShareAlike 4.0 International - https://creativecommons.org/licenses/by-sa/4.0
irf-7103: Copyright & License
This library is licensed under the General Public License, Version 2.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
